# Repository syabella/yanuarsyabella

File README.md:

# yanuarsyabella
schematic, layout, design box, arduino program, matlab fuzzy

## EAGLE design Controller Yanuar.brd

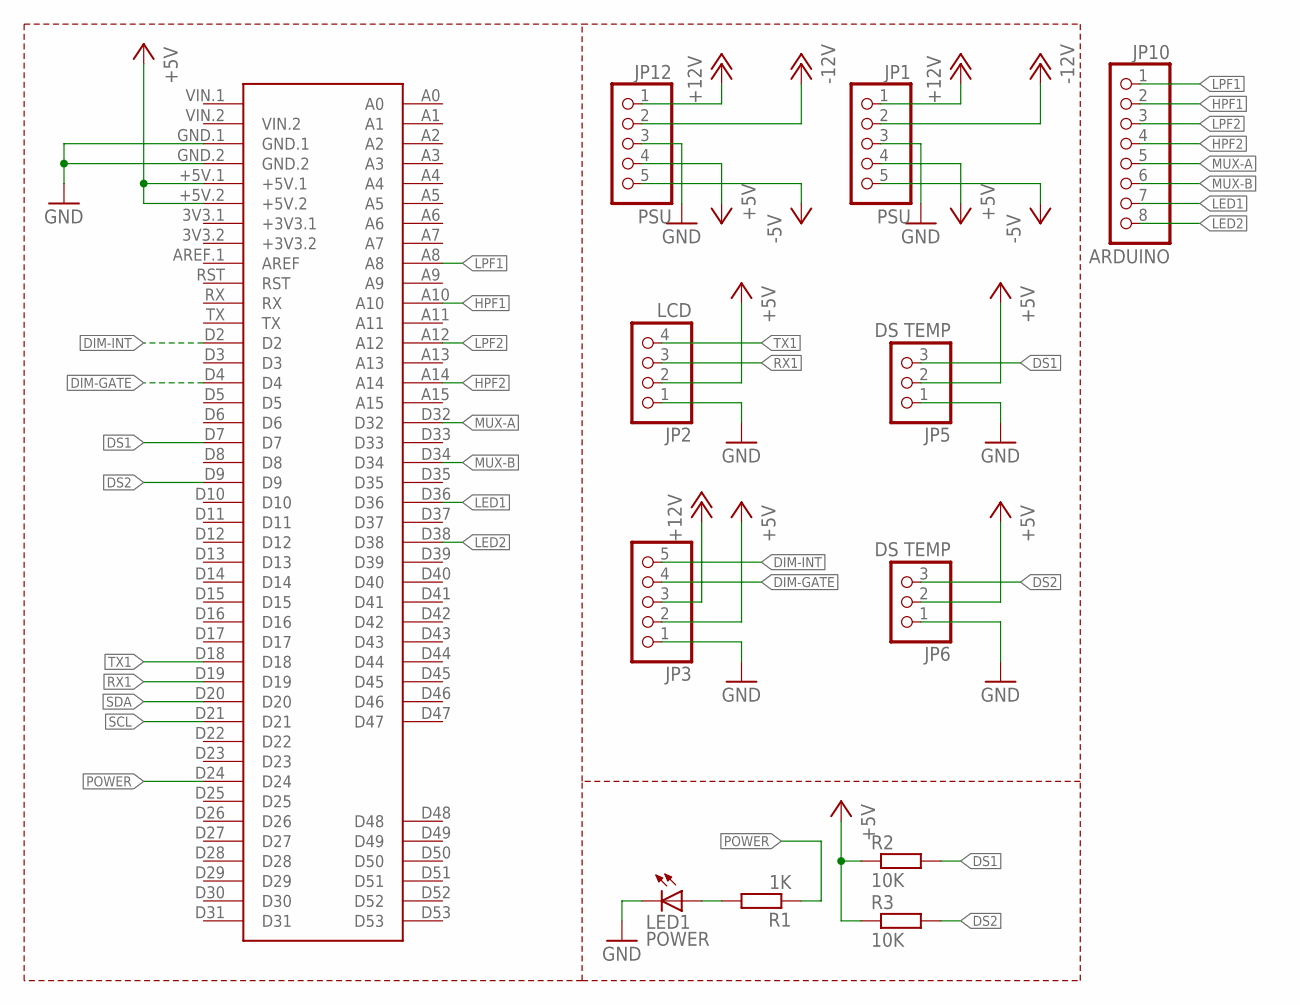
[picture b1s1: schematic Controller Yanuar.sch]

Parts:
JP1, JP12: PSU; 1X05
JP2: LCD; 1X04
JP3: PINHD-1X5"; 1X05
JP5, JP6: DS TEMP; 1X03
JP10: ARDUINO; 1X08
LED1: POWER; LED3MM
R1: 1K; 0207/7
R2, R3: 10K; 0207/15
U$1: MEGA2560_MIKRO

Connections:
+5V: JP1.4, JP2.2, JP3.2, JP5.2, JP6.2, JP12.4, R2.1, R3.1, U$1.+5V.1, U$1.+5V.2
+12V: JP1.1, JP3.3, JP12.1
-5V: JP1.5, JP12.5
-12V: JP1.2, JP12.2
DIM-GATE: JP3.4, U$1.D4
DIM-INT: JP3.5, U$1.D2
DS1: JP5.3, R2.2, U$1.D7
DS2: JP6.3, R3.2, U$1.D9
GND: JP1.3, JP2.1, JP3.1, JP5.1, JP6.1, JP12.3, LED1.K (C), U$1.GND.1, U$1.GND.2
HPF1: JP10.2, U$1.A10
HPF2: JP10.4, U$1.A14
LED1: JP10.7, U$1.D36
LED2: JP10.8, U$1.D38
LPF1: JP10.1, U$1.A8
LPF2: JP10.3, U$1.A12
MUX-A: JP10.5, U$1.D32
MUX-B: JP10.6, U$1.D34
unnamed: LED1.A, R1.2
POWER: R1.1, U$1.D24
RX1: JP2.3, U$1.D19
SCL: U$1.D21
SDA: U$1.D20
TX1: JP2.4, U$1.D18

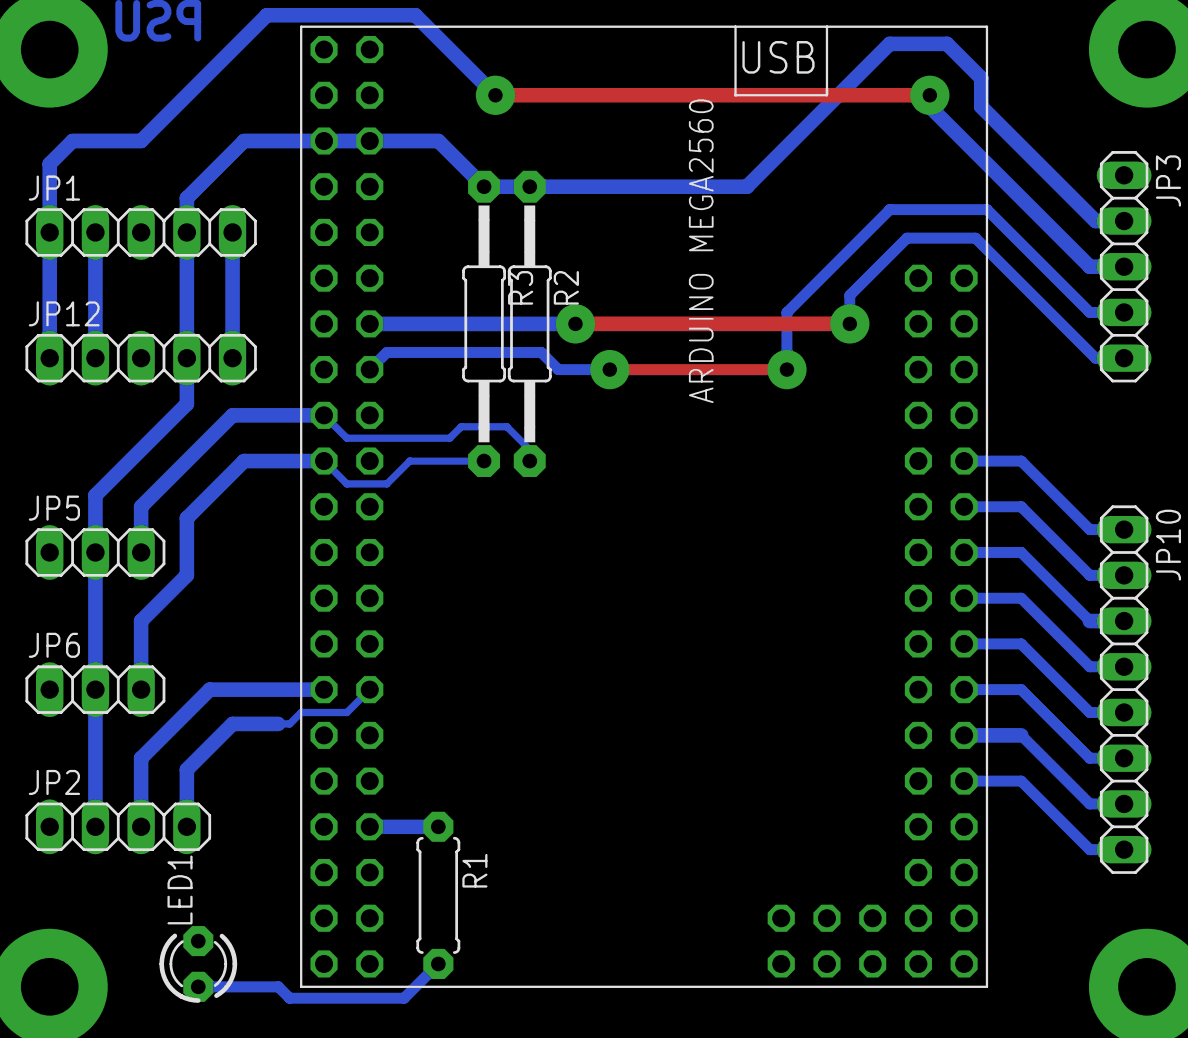
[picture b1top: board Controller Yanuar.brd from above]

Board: 2 copper layers, 12 parts (0 on the bottom side), 21 nets.

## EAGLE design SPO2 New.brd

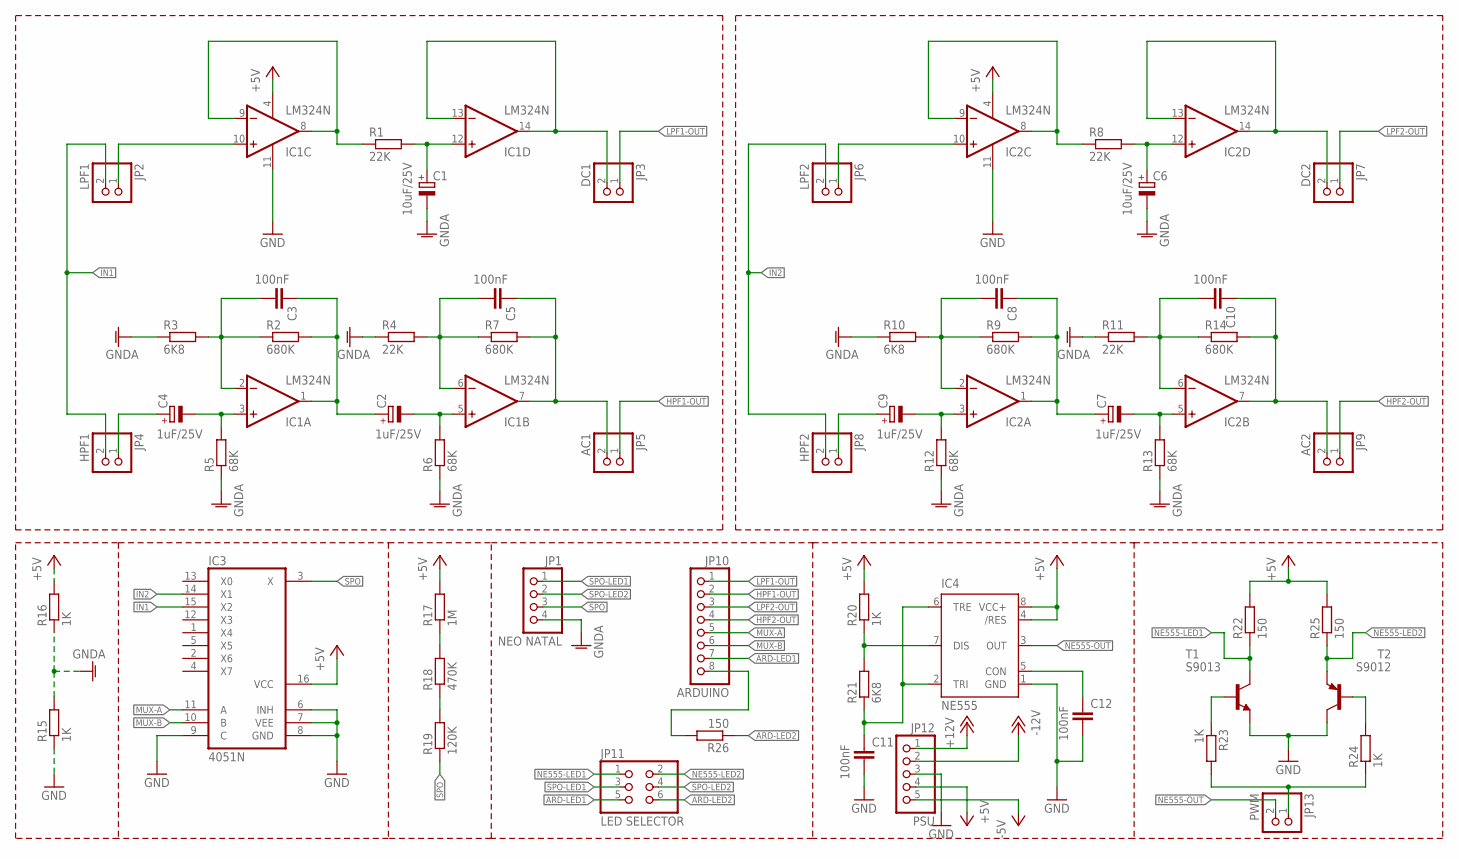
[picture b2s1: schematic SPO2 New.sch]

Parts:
C1, C6: 10uF/25V; E2,5-6
C2, C4, C7, C9: 1uF/25V; E2,5-6
C3, C5, C8, C10, C11, C12: 100nF; C050-025X075
IC1, IC2: LM324N; DIL14
IC3: 4051N; DIL16
IC4: NE555; DIL-08
JP1: NEO NATAL; 1X04
JP2: LPF1; 1X02
JP3: DC1; 1X02
JP4: HPF1; 1X02
JP5: AC1; 1X02
JP6: LPF2; 1X02
JP7: DC2; 1X02
JP8: HPF2; 1X02
JP9: AC2; 1X02
JP10: ARDUINO; 1X08
JP11: LED SELECTOR; 2X03
JP12: PSU; 1X05
JP13: PWM; 1X02
R1, R4, R8, R11: 22K; 0207/7
R2, R7, R9, R14: 680K; 0207/7
R3, R10, R21: 6K8; 0207/7
R5, R6, R12, R13: 68K; 0207/7
R15, R16, R20, R23, R24: 1K; 0207/7
R17: 1M; 0207/7
R18: 470K; 0207/7
R19: 120K; 0207/7
R22, R25, R26: 150; 0207/7
T1: S9013; TO92-EBC
T2: S9012; TO92-EBC

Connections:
+5V: IC1.4 (V+), IC2.4 (V+), IC3.16 (VCC), IC4.4 (/RES), IC4.8 (VCC+), JP12.4, R16.2, R17.2, R20.2, R22.2, R25.2
+12V: JP12.1
-5V: JP12.5
-12V: JP12.2
ARD-LED1: JP10.7, JP11.5
ARD-LED2: JP11.6, R26.1
GND: C11.2, C12.2, IC1.11 (V-), IC2.11 (V-), IC3.6 (INH), IC3.7 (VEE), IC3.8 (GND), IC3.9 (C), IC4.1 (GND), JP12.3, R15.1, T1.E, T2.C
GNDA: C1.-, C6.-, JP1.4, R3.1, R4.1, R5.1, R6.1, R10.1, R11.1, R12.1, R13.1, R15.2, R16.1
HPF1-OUT: JP5.1, JP10.2
HPF2-OUT: JP9.1, JP10.4
IN1: IC3.15 (X2), JP2.2, JP4.2
IN2: IC3.14 (X1), JP6.2, JP8.2
LPF1-OUT: JP3.1, JP10.1
LPF2-OUT: JP7.1, JP10.3
MUX-A: IC3.11 (A), JP10.5
MUX-B: IC3.10 (B), JP10.6
unnamed: C1.+, IC1.12 (+IN), R1.2
unnamed: IC1.13 (-IN), IC1.14 (OUT), JP3.2
unnamed: IC1.8 (OUT), IC1.9 (-IN), R1.1
unnamed: IC1.10 (+IN), JP2.1
unnamed: C6.+, IC2.12 (+IN), R8.2
unnamed: IC2.8 (OUT), IC2.9 (-IN), R8.1
unnamed: C3.2, IC1.2 (-IN), R2.1, R3.2
unnamed: C5.2, IC1.6 (-IN), R4.2, R7.1
unnamed: C2.+, C3.1, IC1.1 (OUT), R2.2
unnamed: C2.-, IC1.5 (+IN), R6.2
unnamed: C4.-, IC1.3 (+IN), R5.2
unnamed: IC2.13 (-IN), IC2.14 (OUT), JP7.2
unnamed: C4.+, JP4.1
unnamed: C8.2, IC2.2 (-IN), R9.1, R10.2
unnamed: C7.+, C8.1, IC2.1 (OUT), R9.2
unnamed: C5.1, IC1.7 (OUT), JP5.2, R7.2
unnamed: C7.-, IC2.5 (+IN), R13.2
unnamed: C10.2, IC2.6 (-IN), R11.2, R14.1
unnamed: C9.-, IC2.3 (+IN), R12.2
unnamed: C9.+, JP8.1
unnamed: C10.1, IC2.7 (OUT), JP9.2, R14.2
unnamed: IC2.10 (+IN), JP6.1
unnamed: IC4.7 (DIS), R20.1, R21.2
unnamed: R18.1, R19.2
unnamed: R17.1, R18.2
unnamed: C11.1, IC4.2 (TRI), IC4.6 (TRE), R21.1
unnamed: C12.1, IC4.5 (CON)
unnamed: R24.2, T2.B
unnamed: R23.1, T1.B
unnamed: JP10.8, R26.2
unnamed: JP13.1, R23.2, R24.1
NE555-LED1: JP11.1, R22.1, T1.C
NE555-LED2: JP11.2, R25.1, T2.E
NE555-OUT: IC4.3 (OUT), JP13.2
SPO: IC3.3 (X), JP1.3, R19.1
SPO-LED1: JP1.1, JP11.3
SPO-LED2: JP1.2, JP11.4

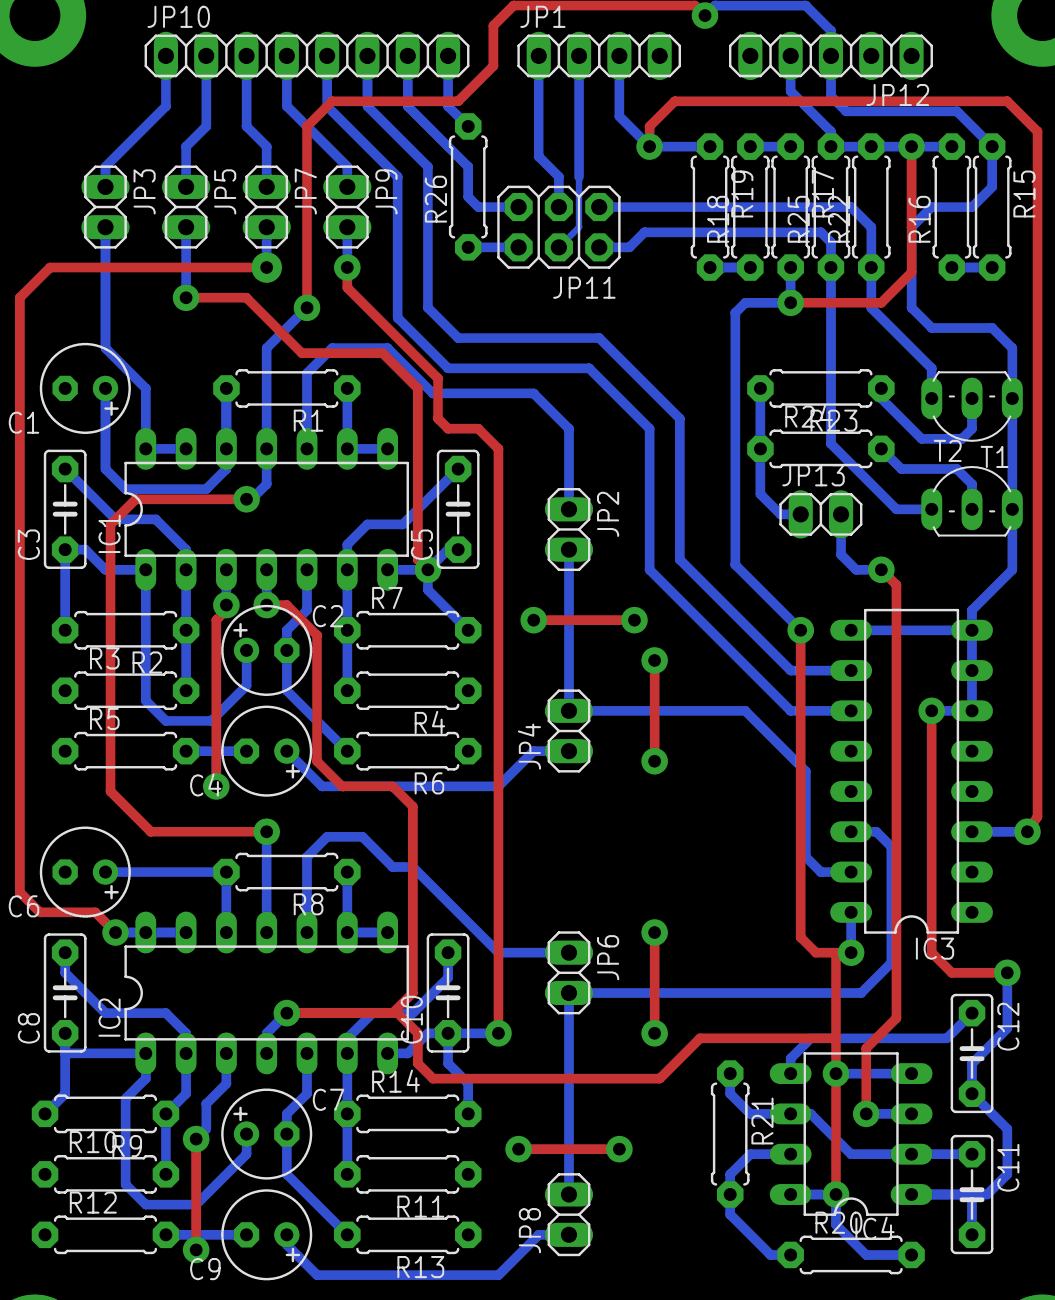
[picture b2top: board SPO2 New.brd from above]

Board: 2 copper layers, 57 parts (0 on the bottom side), 50 nets.

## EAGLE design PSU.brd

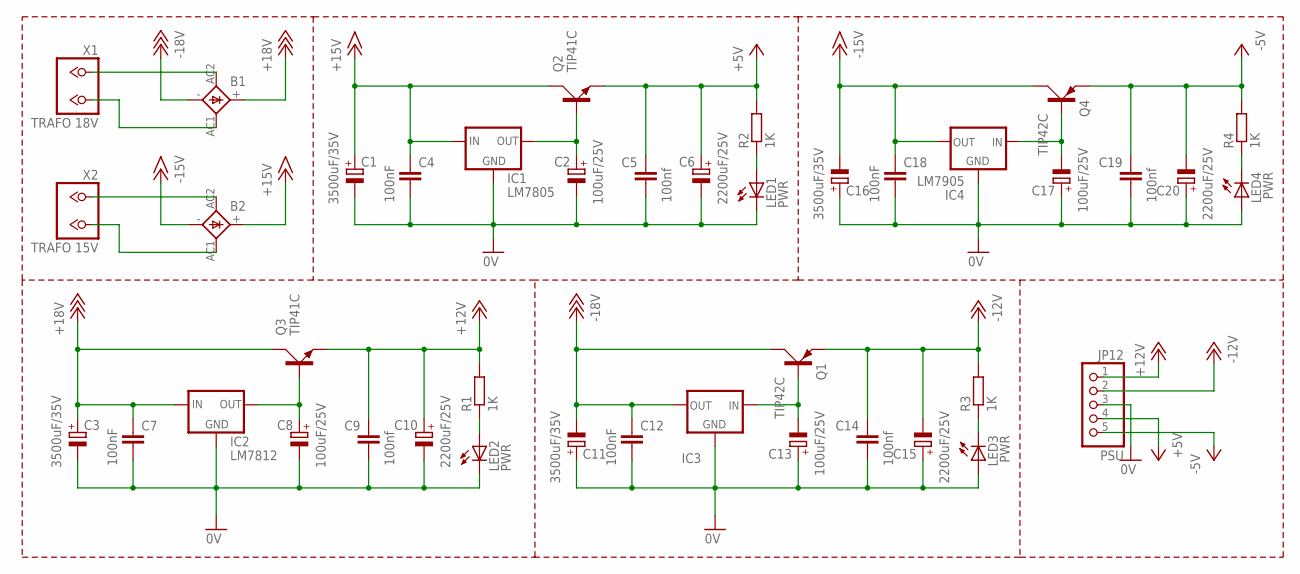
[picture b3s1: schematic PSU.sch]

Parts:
B1, B2: KBL
C1, C3, C11, C16: 3500uF/35V; EB20D
C2, C8, C13, C17: 100uF/25V; E2,5-7
C4, C7, C12, C18: 100nF; C050-025X075
C5, C9, C14, C19: 100nf; C050-025X075
C6, C10, C15, C20: 2200uF/25V; E5-13
IC1: LM7805; 78XXS
IC2: LM7812; 78XXS
IC3: 79XXS
IC4: LM7905; 79XXS
JP12: PSU; 1X05
LED1, LED2, LED3, LED4: PWR; LED3MM
Q1, Q4: TIP42C; TO220AV
Q2, Q3: TIP41C; TO220AV
R1, R2, R3, R4: 1K; 0207/7
X1: TRAFO 18V; TB2
X2: TRAFO 15V; TB2

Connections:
0V: C1.-, C2.-, C3.-, C4.2, C5.2, C6.-, C7.2, C8.-, C9.2, C10.-, C11.+, C12.2, C13.+, C14.2, C15.+, C16.+, C17.+, C18.2, C19.2, C20.+, IC1.GND, IC2.GND, IC3.GND, IC4.GND, JP12.3, LED1.K (C), LED2.K (C), LED3.A, LED4.A
+5V: C5.1, C6.+, JP12.4, Q2.E, R2.2
+12V: C9.1, C10.+, JP12.1, Q3.E, R1.2
+15V: B2.+, C1.+, C4.1, IC1.IN, Q2.C
+18V: B1.+, C3.+, C7.1, IC2.IN, Q3.C
-5V: C19.1, C20.-, JP12.5, Q4.E, R4.2
-12V: C14.1, C15.-, JP12.2, Q1.E, R3.2
-15V: B2.-, C16.-, C18.1, IC4.OUT, Q4.C
-18V: B1.-, C11.-, C12.1, IC3.OUT, Q1.C
unnamed: B1.AC1 (AC2), X1.2
unnamed: B1.AC2 (AC1), X1.1
unnamed: C13.-, IC3.IN, Q1.B
unnamed: LED1.A, R2.1
unnamed: C8.+, IC2.OUT, Q3.B
unnamed: C2.+, IC1.OUT, Q2.B
unnamed: LED2.A, R1.1
unnamed: LED3.K (C), R3.1
unnamed: C17.-, IC4.IN, Q4.B
unnamed: LED4.K (C), R4.1
unnamed: B2.AC2 (AC1), X2.1
unnamed: B2.AC1 (AC2), X2.2

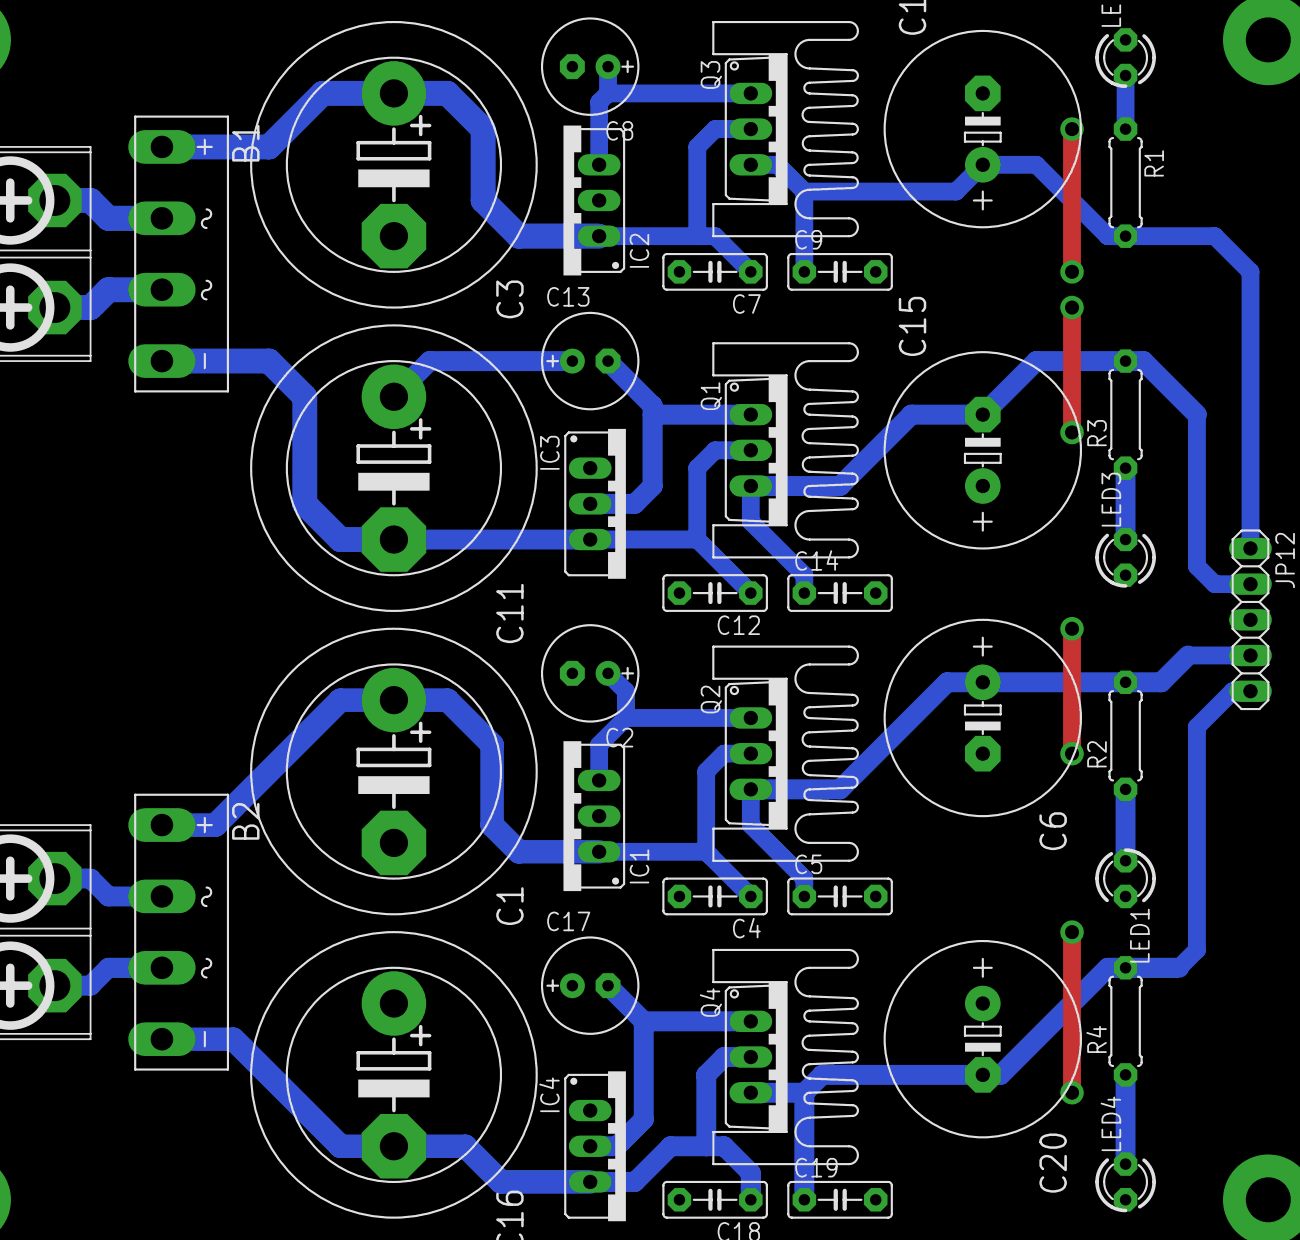
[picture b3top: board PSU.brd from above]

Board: 2 copper layers, 45 parts (0 on the bottom side), 21 nets.

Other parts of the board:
U$1, U$2, U$3, U$4: SK95-2M3
